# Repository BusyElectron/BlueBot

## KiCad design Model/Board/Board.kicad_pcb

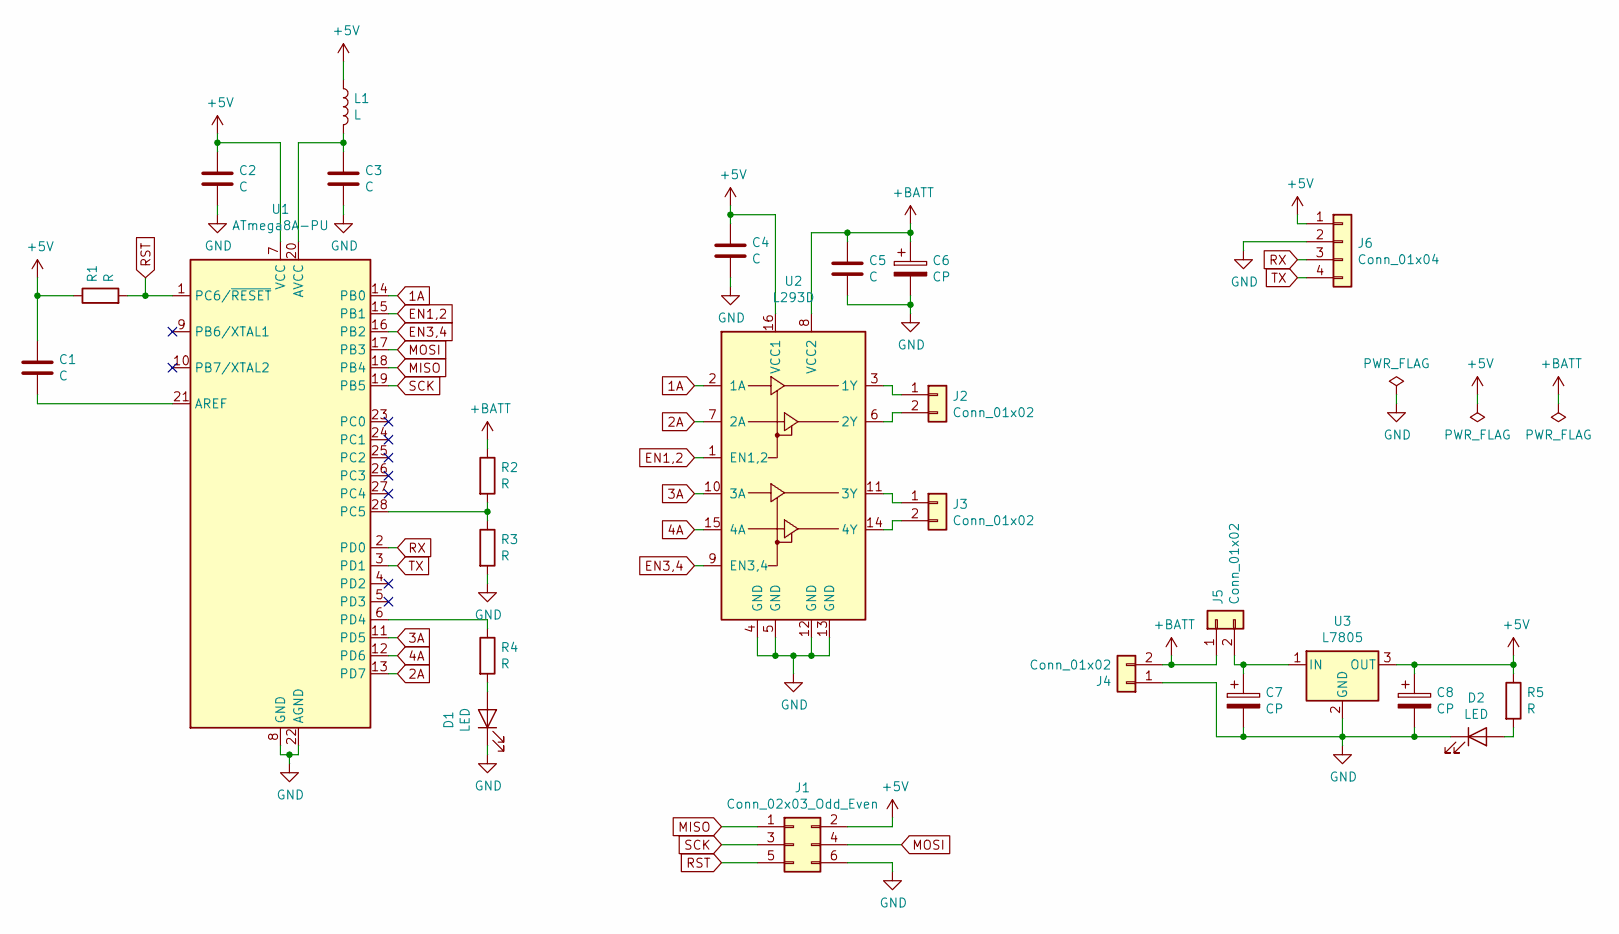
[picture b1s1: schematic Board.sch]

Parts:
C1, C2, C3, C4, C5: C; C_Disc_D6.0mm_W2.5mm_P5.00mm
C6, C7, C8: CP; C_Radial_D5.0mm_H11.0mm_P2.00mm
D1, D2: LED; LED_D5.0mm
J1: Conn_02x03_Odd_Even; PinHeader_2x03_P2.54mm_Horizontal
J2, J3, J4, J5: Conn_01x02; PinHeader_1x02_P2.54mm_Vertical
J6: Conn_01x04; PinHeader_1x04_P2.54mm_Vertical
L1: L; L_Axial_L5.3mm_D2.2mm_P10.16mm_Horizontal_Vishay_IM-1
R1, R2, R3, R4, R5: R; R_Axial_DIN0207_L6.3mm_D2.5mm_P10.16mm_Horizontal
U1: ATmega8A-PU; DIP-28_W7.62mm
U2: L293D; DIP-16_W7.62mm
U3: L7805; TO-220-3_Horizontal_TabDown

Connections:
1A: U1.14 (PB0), U2.2 (1A)
2A: U1.13 (PD7), U2.7 (2A)
3A: U1.11 (PD5), U2.10 (3A)
4A: U1.12 (PD6), U2.15 (4A)
+5V: C1.1, C2.1, C4.1, C8.1, J1.2, J6.1, L1.1, R1.1, R5.1, U1.7 (VCC), U2.16 (VCC1), U3.3 (OUT)
+BATT: C5.1, C6.1, J4.2, J5.1, R2.1, U2.8 (VCC2)
EN1,2: U1.15 (PB1), U2.1 (EN1,2)
EN3,4: U1.16 (PB2), U2.9 (EN3,4)
GND: C2.2, C3.2, C4.2, C5.2, C6.2, C7.2, C8.2, D1.1 (K), D2.1 (K), J1.6, J4.1, J6.2, R3.2, U1.8 (GND), U1.22 (AGND), U2.4 (GND), U2.5 (GND), U2.12 (GND), U2.13 (GND), U3.2 (GND)
MISO: J1.1, U1.18 (PB4)
MOSI: J1.4, U1.17 (PB3)
unnamed: C1.2, U1.21 (AREF)
unnamed: C3.1, L1.2, U1.20 (AVCC)
unnamed: C7.1, J5.2, U3.1 (IN)
unnamed: D1.2 (A), R4.2
unnamed: D2.2 (A), R5.2
unnamed: J2.1, U2.3 (1Y)
unnamed: J2.2, U2.6 (2Y)
unnamed: J3.1, U2.11 (3Y)
unnamed: J3.2, U2.14 (4Y)
unnamed: R2.2, R3.1, U1.28 (PC5)
unnamed: R4.1, U1.6 (PD4)
RST: J1.5, R1.2, U1.1 (PC6/~RESET)
RX: J6.3, U1.2 (PD0)
SCK: J1.3, U1.19 (PB5)
TX: J6.4, U1.3 (PD1)

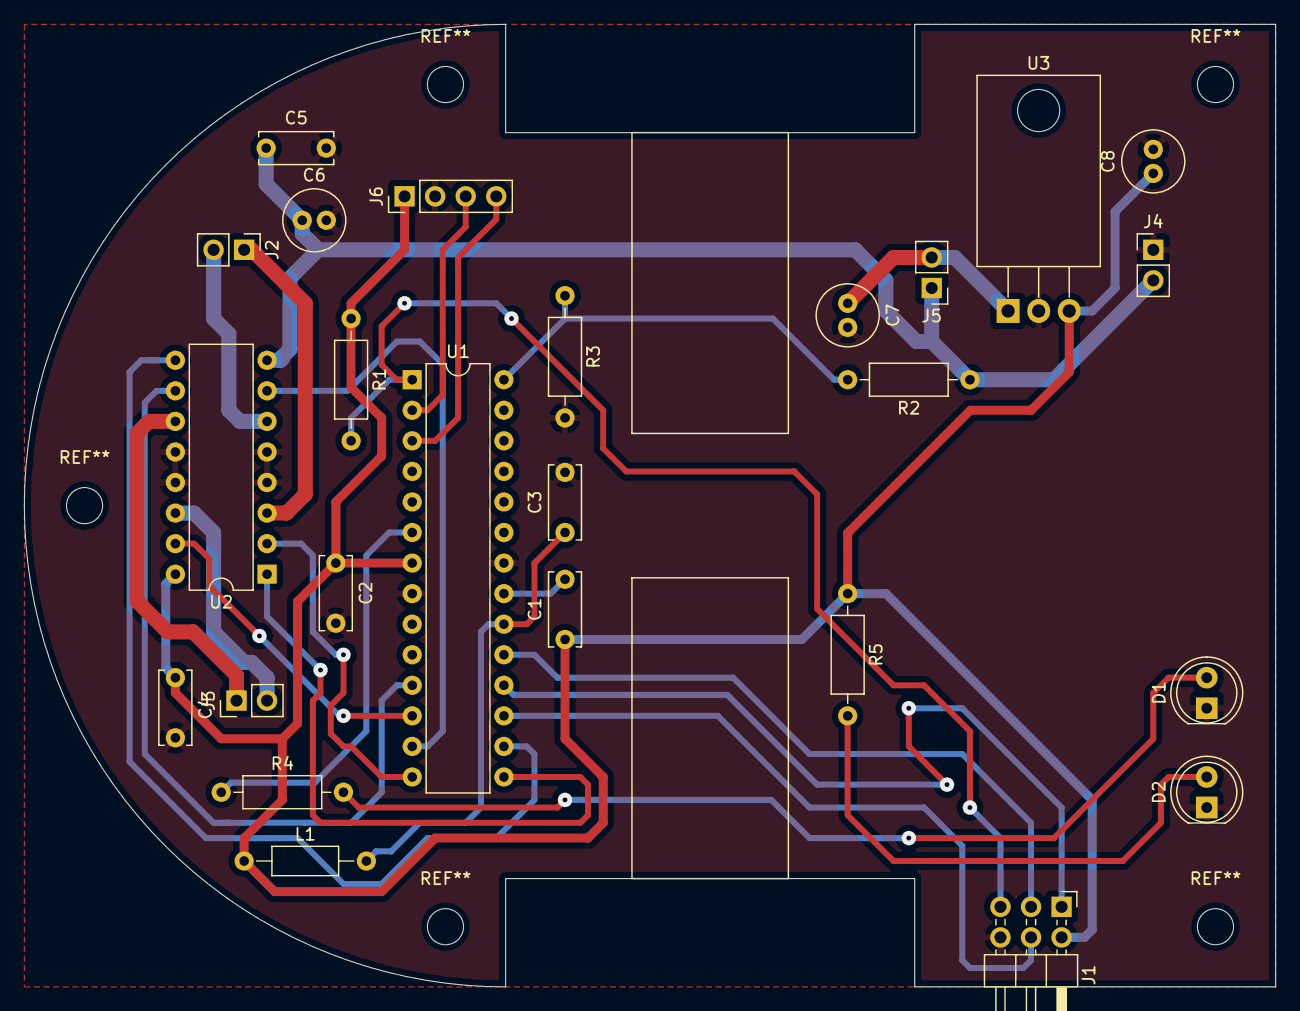
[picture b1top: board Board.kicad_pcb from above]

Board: 2 copper layers, 104.0 x 80.0 mm, 25 parts (0 on the bottom side), 26 nets.

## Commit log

2019-07-04 Add cover file
